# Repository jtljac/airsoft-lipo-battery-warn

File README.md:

A quick implementation for a Attiny85 based LiPo low charge warning system.

Includes an LED for indicating >50% charge, and a buzzer for the danger zone.

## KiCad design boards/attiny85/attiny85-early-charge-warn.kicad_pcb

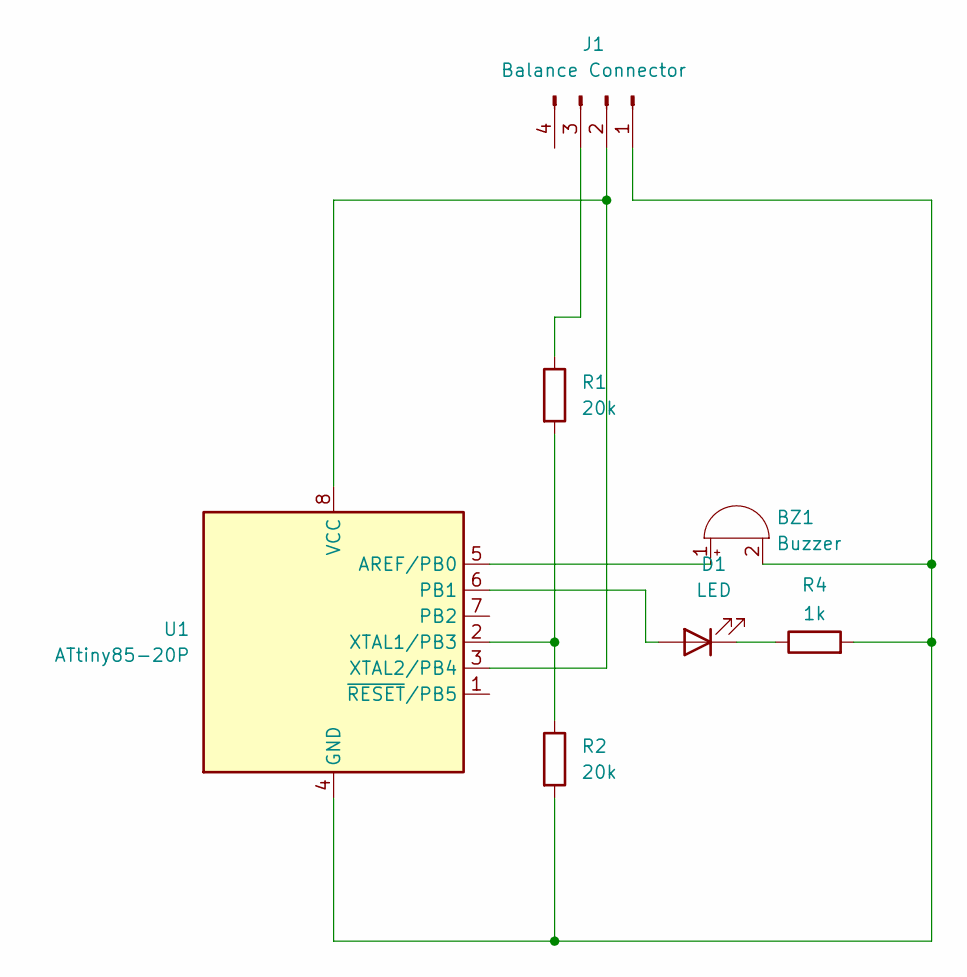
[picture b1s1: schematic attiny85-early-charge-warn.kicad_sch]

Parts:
BZ1: Buzzer; Buzzer_12x9.5RM7.6
D1: LED; LED_D3.0mm
J1: Balance Connector; PinHeader_1x04_P2.54mm_Horizontal
R1, R2: 20k; R_Axial_DIN0204_L3.6mm_D1.6mm_P7.62mm_Horizontal
R4: 1k; R_Axial_DIN0204_L3.6mm_D1.6mm_P7.62mm_Horizontal
U1: ATtiny85-20P; DIP-8_W7.62mm

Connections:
unnamed: BZ1.1 (+), U1.5 (AREF/PB0)
unnamed: BZ1.2 (-), J1.1, R2.2, R4.2, U1.4 (GND)
unnamed: D1.2 (A), U1.6 (PB1)
unnamed: D1.1 (K), R4.1
unnamed: J1.2, U1.3 (XTAL2/PB4), U1.8 (VCC)
unnamed: J1.3, R1.1
unnamed: R1.2, R2.1, U1.2 (XTAL1/PB3)

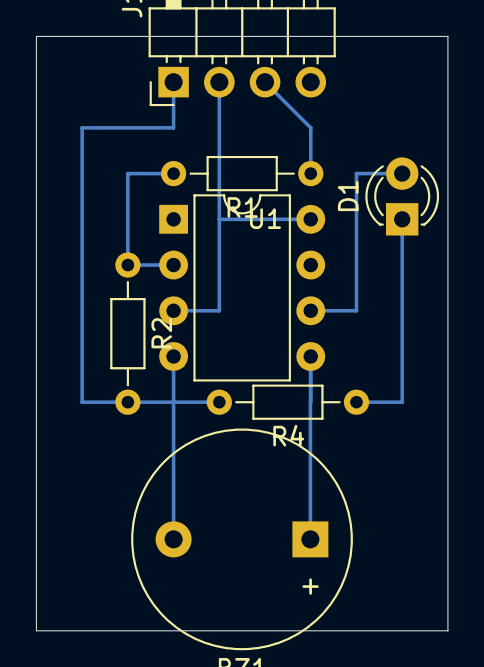
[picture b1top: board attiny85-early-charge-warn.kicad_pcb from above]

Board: 2 copper layers, 22.9 x 33.0 mm, 7 parts (0 on the bottom side), 7 nets.
